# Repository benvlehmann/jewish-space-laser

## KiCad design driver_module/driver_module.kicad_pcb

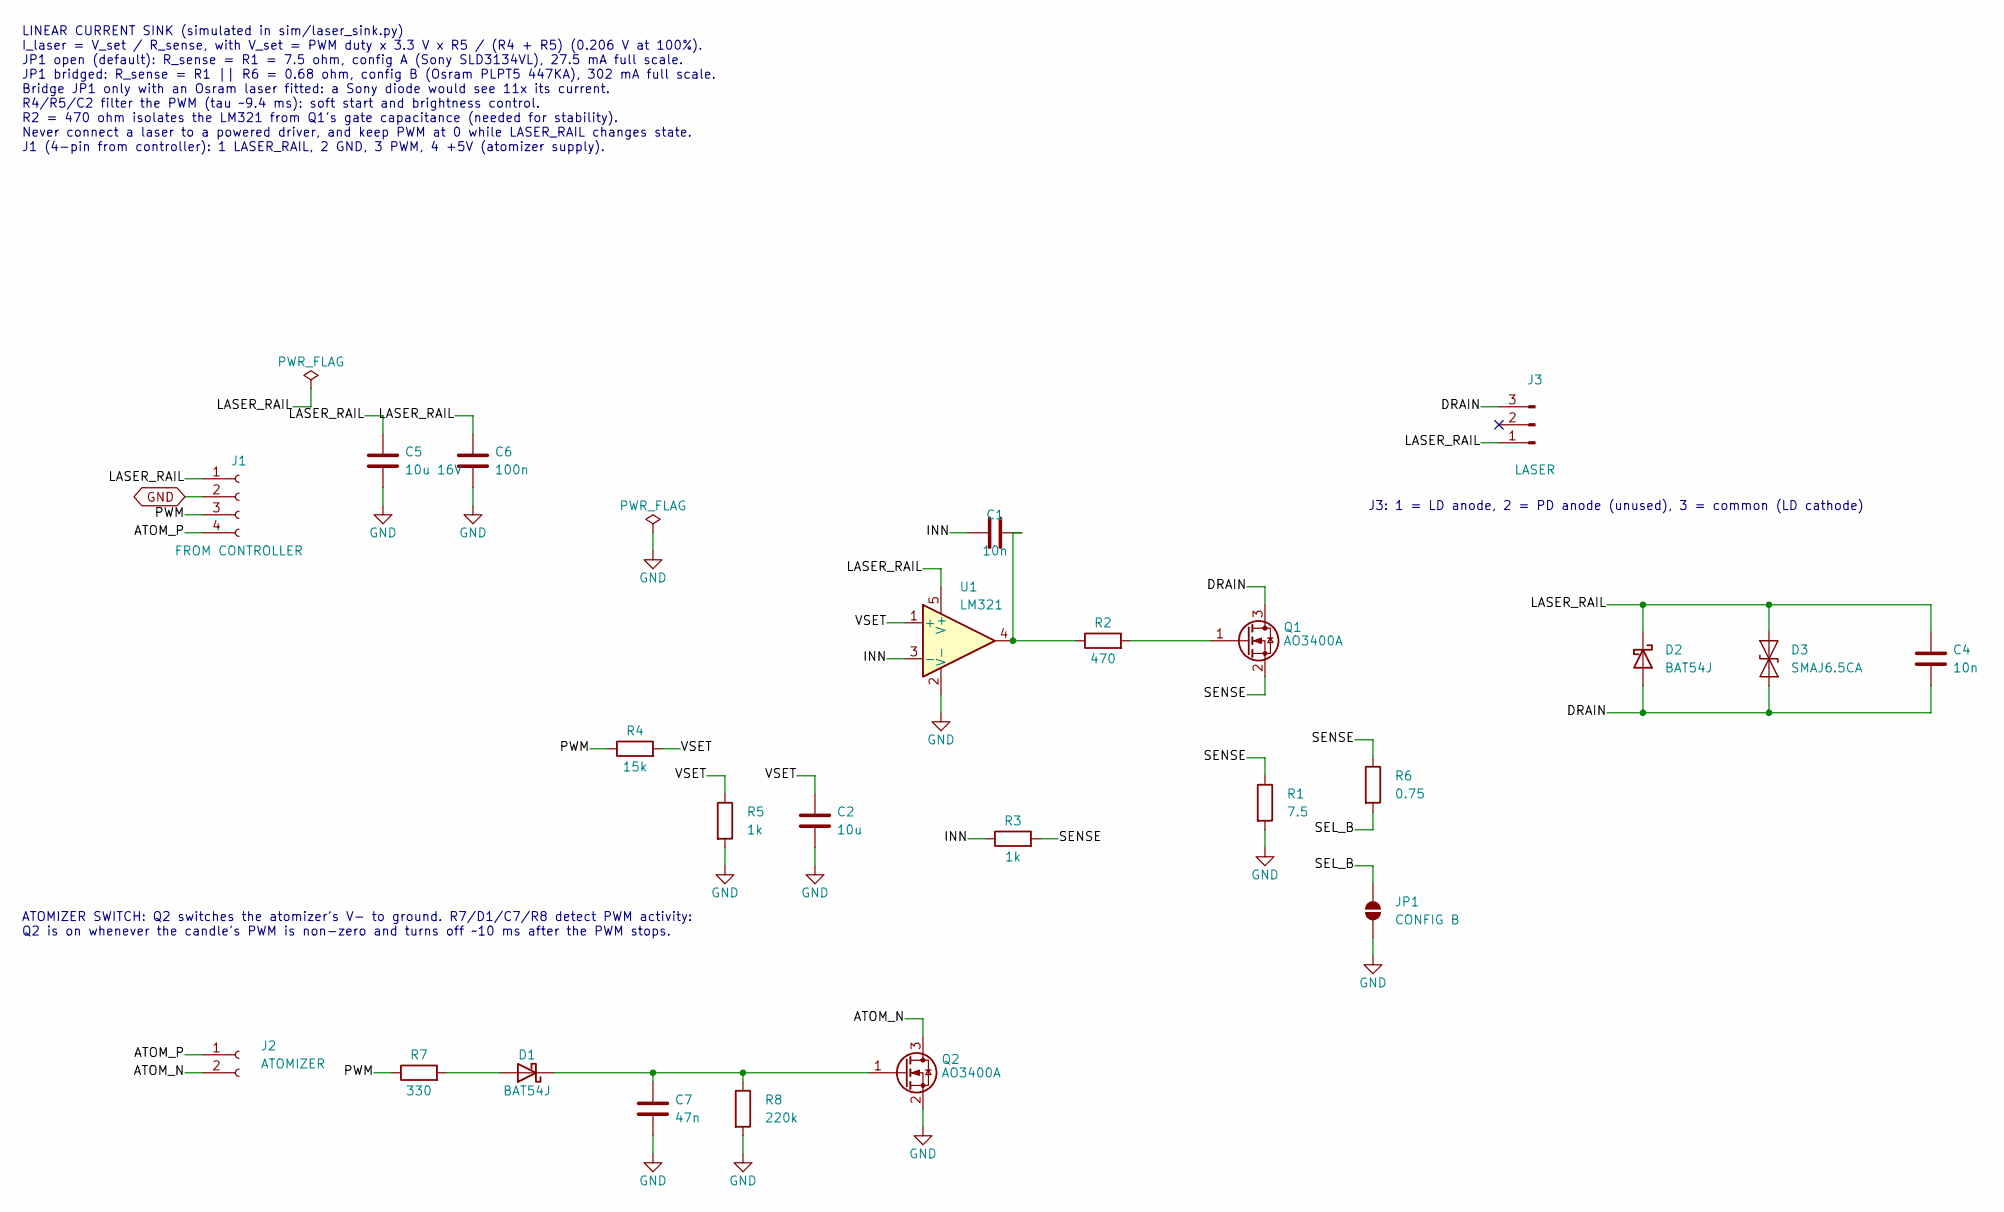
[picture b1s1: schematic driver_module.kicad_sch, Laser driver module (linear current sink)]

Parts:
C1, C4: 10n; C_0805_2012Metric_Pad1.18x1.45mm_HandSolder
C2: 10u; C_0805_2012Metric_Pad1.18x1.45mm_HandSolder
C5: 10u 16V; C_0805_2012Metric_Pad1.18x1.45mm_HandSolder
C6: 100n; C_0805_2012Metric_Pad1.18x1.45mm_HandSolder
C7: 47n; C_0805_2012Metric_Pad1.18x1.45mm_HandSolder
D1, D2: BAT54J; D_SOD-323F
D3: SMAJ6.5CA; D_SMA
J1: FROM CONTROLLER; JST_ZH_B4B-ZR_1x04_P1.50mm_Vertical
J2: ATOMIZER; JST_ZH_B2B-ZR_1x02_P1.50mm_Vertical
J3: LASER; JST_ZH_B3B-ZR_1x03_P1.50mm_Vertical
JP1: CONFIG B; SolderJumper-2_P1.3mm_Open_RoundedPad1.0x1.5mm
Q1, Q2: AO3400A; SOT-23
R1: 7.5; R_0805_2012Metric_Pad1.20x1.40mm_HandSolder
R2: 470; R_0805_2012Metric_Pad1.20x1.40mm_HandSolder
R3, R5: 1k; R_0805_2012Metric_Pad1.20x1.40mm_HandSolder
R4: 15k; R_0805_2012Metric_Pad1.20x1.40mm_HandSolder
R6: 0.75; R_0805_2012Metric_Pad1.20x1.40mm_HandSolder
R7: 330; R_0805_2012Metric_Pad1.20x1.40mm_HandSolder
R8: 220k; R_0805_2012Metric_Pad1.20x1.40mm_HandSolder
U1: LM321; SOT-23-5

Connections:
/ATOM_N: J2.2, Q2.3 (D)
/ATOM_P: J1.4, J2.1
/DRAIN: C4.2, D2.2 (A), D3.2 (A2), J3.3, Q1.3 (D)
/INN: C1.1, R3.1, U1.3 (-)
/LASER_RAIL: C4.1, C5.1, C6.1, D2.1 (K), D3.1 (A1), J1.1, J3.1, U1.5 (V+)
/PWM: J1.3, R4.1, R7.1
/SEL_B: JP1.1 (A), R6.2
/SENSE: Q1.2 (S), R1.1, R3.2, R6.1
/VSET: C2.1, R4.2, R5.1, U1.1 (+)
GND: C2.2, C5.2, C6.2, C7.2, J1.2, JP1.2 (B), Q2.2 (S), R1.2, R5.2, R8.2, U1.2 (V-)
unnamed: C1.2, R2.1, U1.4
unnamed: D1.2 (A), R7.2
unnamed: C7.1, D1.1 (K), Q2.1 (G), R8.1
unnamed: Q1.1 (G), R2.2

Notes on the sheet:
LINEAR CURRENT SINK (simulated in sim/laser_sink.py) I_laser = V_set / R_sense, with V_set = PWM duty x 3.3 V x R5 / (R4 + R5) (0.206 V at 100%). JP1 open (default): R_sense = R1 = 7.5 ohm, config A (Sony SLD3134VL), 27.5 mA full scale. JP1 bridged: R_sense = R1 || R6 = 0.68 ohm, config B (Osram PL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
J3: 1 = LD anode, 2 = PD anode (unused), 3 = common (LD cathode)
ATOMIZER SWITCH: Q2 switches the atomizer's V- to ground. R7/D1/C7/R8 detect PWM activity: Q2 is on whenever the candle's PWM is non-zero and turns off ~10 ms after the PWM stops.

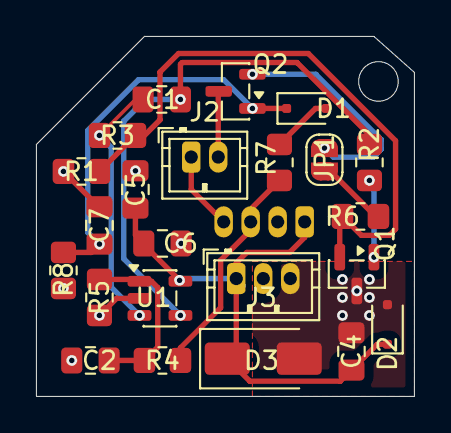
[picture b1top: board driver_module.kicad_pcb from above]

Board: 2 copper layers, 21.0 x 20.0 mm, 25 parts (1 on the bottom side), 14 nets.

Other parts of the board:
H1: MountingHole_2.2mm_M2

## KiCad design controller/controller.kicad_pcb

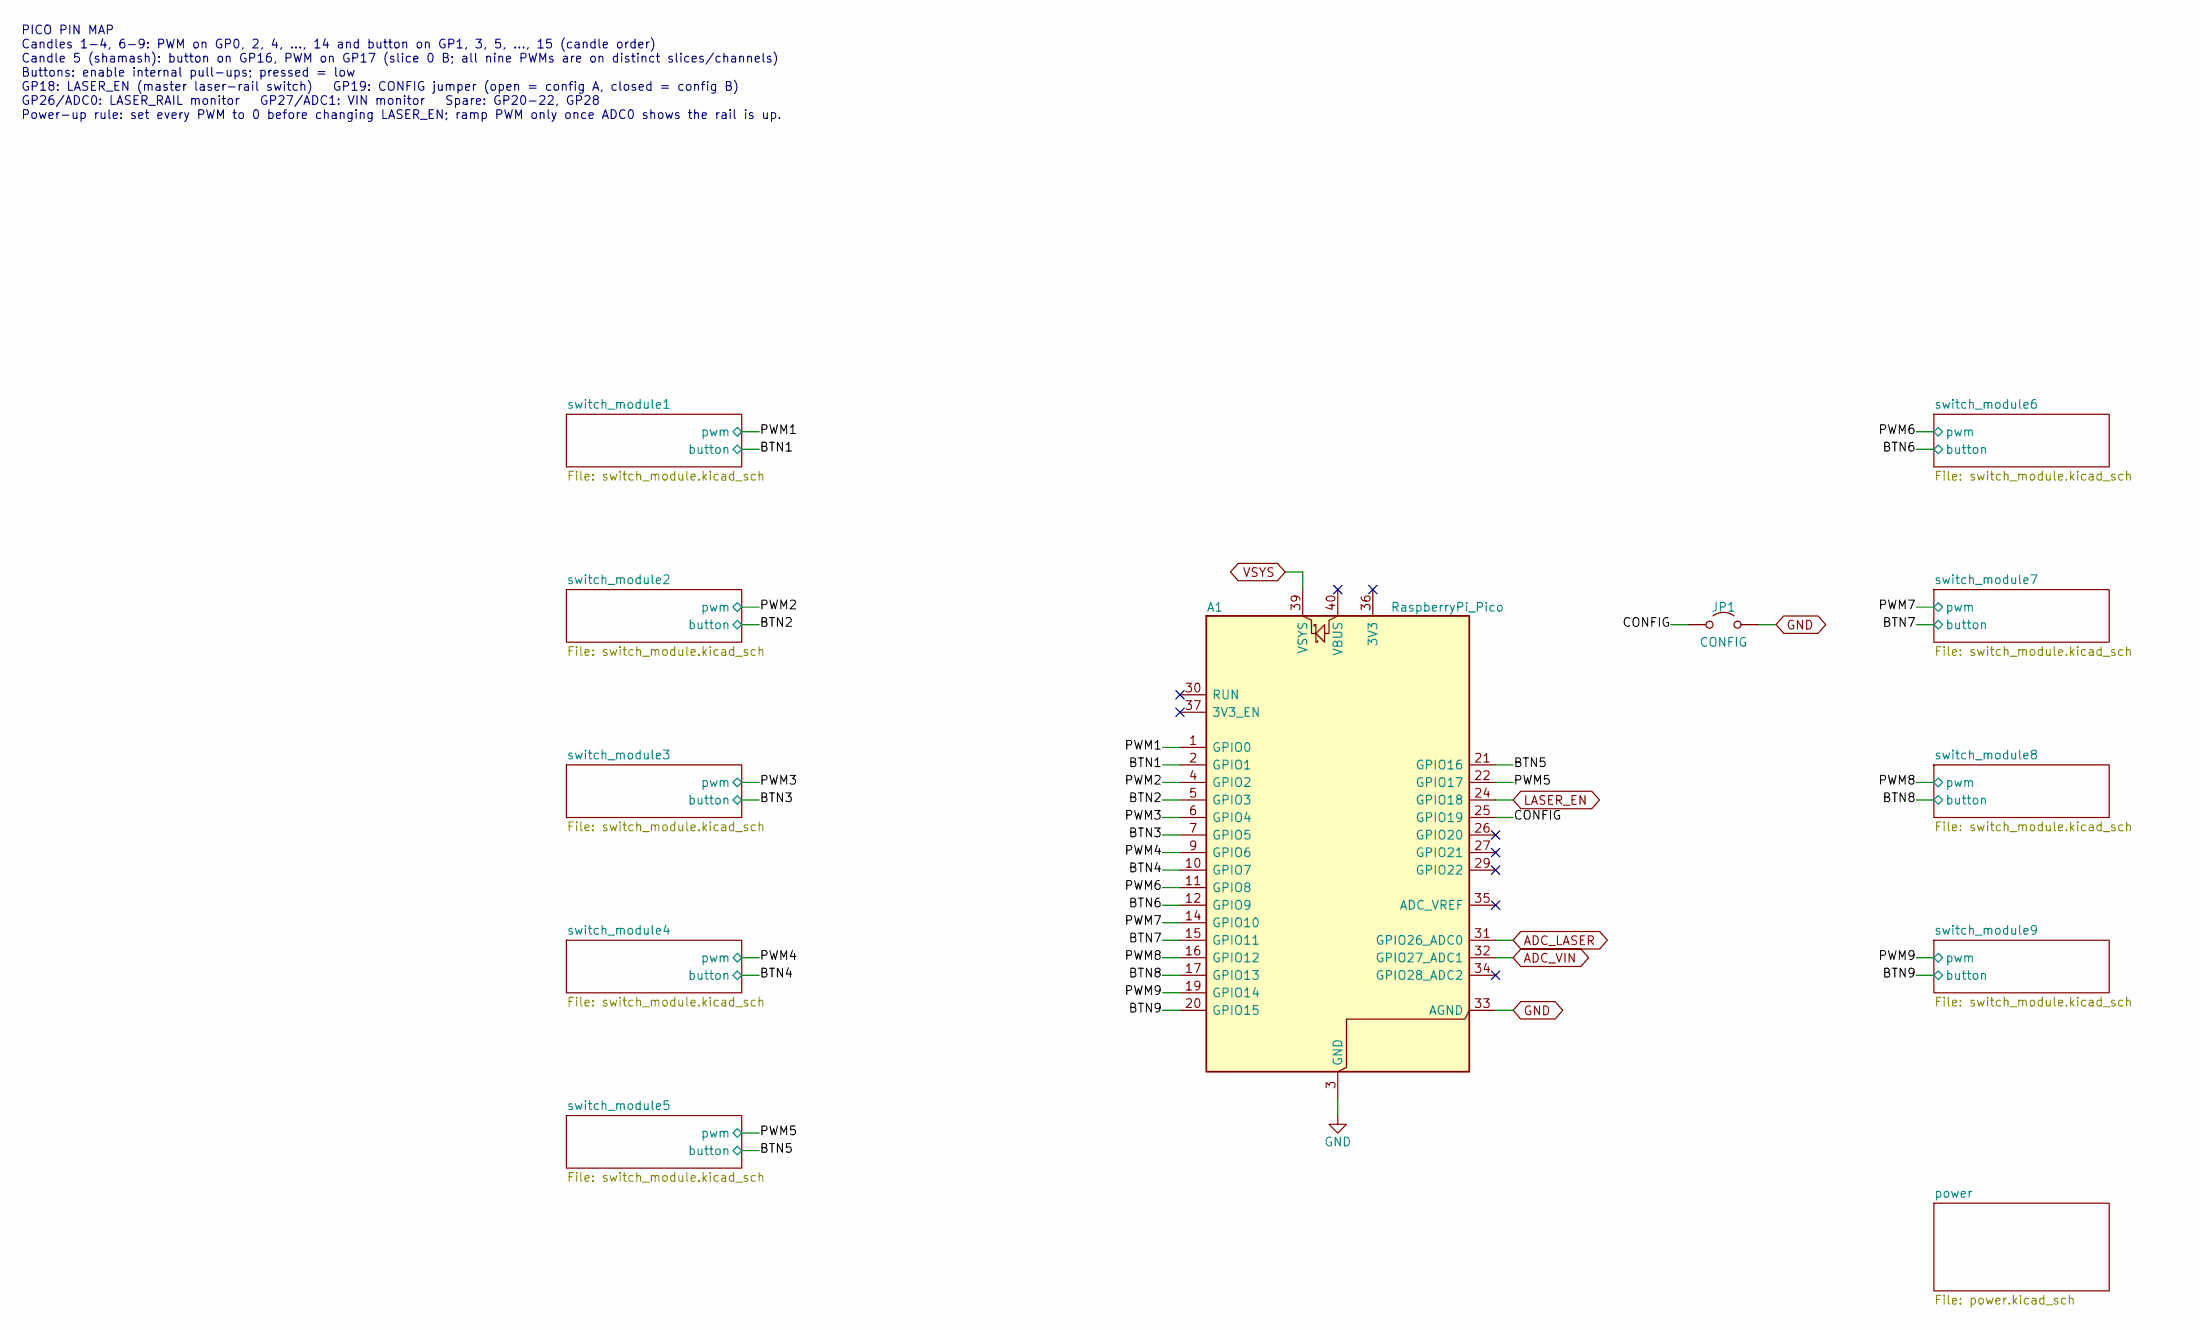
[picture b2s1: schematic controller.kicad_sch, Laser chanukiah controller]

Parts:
A1: RaspberryPi_Pico; RaspberryPi_Pico_Common_Unspecified
JP1: CONFIG; PinHeader_1x02_P2.54mm_Vertical

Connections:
/BTN1: A1.2 (GPIO1); also elsewhere on the board
/BTN2: A1.5 (GPIO3); also elsewhere on the board
/BTN3: A1.7 (GPIO5); also elsewhere on the board
/BTN4: A1.10 (GPIO7); also elsewhere on the board
/BTN5: A1.21 (GPIO16); also elsewhere on the board
/BTN6: A1.12 (GPIO9); also elsewhere on the board
/BTN7: A1.15 (GPIO11); also elsewhere on the board
/BTN8: A1.17 (GPIO13); also elsewhere on the board
/BTN9: A1.20 (GPIO15); also elsewhere on the board
/CONFIG: A1.25 (GPIO19), JP1.1 (A)
/PWM1: A1.1 (GPIO0); also elsewhere on the board
/PWM2: A1.4 (GPIO2); also elsewhere on the board
/PWM3: A1.6 (GPIO4); also elsewhere on the board
/PWM4: A1.9 (GPIO6); also elsewhere on the board
/PWM5: A1.22 (GPIO17); also elsewhere on the board
/PWM6: A1.11 (GPIO8); also elsewhere on the board
/PWM7: A1.14 (GPIO10); also elsewhere on the board
/PWM8: A1.16 (GPIO12); also elsewhere on the board
/PWM9: A1.19 (GPIO14); also elsewhere on the board
ADC_LASER: A1.31 (GPIO26_ADC0); also elsewhere on the board
ADC_VIN: A1.32 (GPIO27_ADC1); also elsewhere on the board
GND: A1.3 (GND), A1.8 (GND), A1.13 (GND), A1.18 (GND), A1.23 (GND), A1.28 (GND), A1.33 (AGND), A1.38 (GND), JP1.2 (B); also elsewhere on the board
LASER_EN: A1.24 (GPIO18); also elsewhere on the board
VSYS: A1.39 (VSYS); also elsewhere on the board

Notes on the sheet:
PICO PIN MAP Candles 1-4, 6-9: PWM on GP0, 2, 4, ..., 14 and button on GP1, 3, 5, ..., 15 (candle order) Candle 5 (shamash): button on GP16, PWM on GP17 (slice 0 B; all nine PWMs are on distinct slices/channels) Buttons: enable internal pull-ups; pressed = low GP18: LASER_EN (master laser-rail swit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

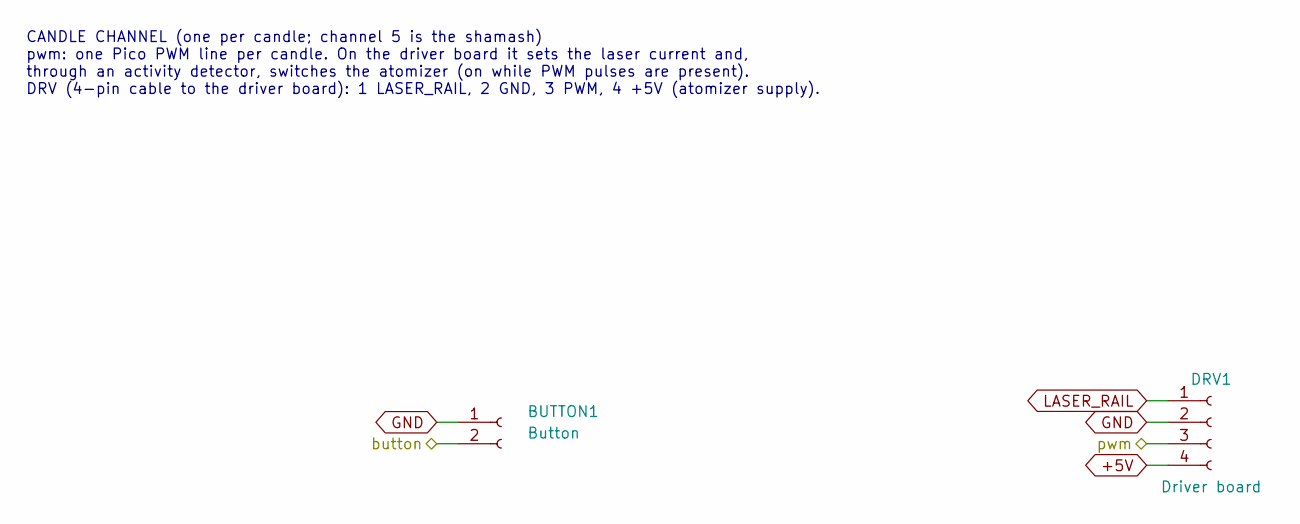
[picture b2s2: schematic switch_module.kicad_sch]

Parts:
BUTTON1: Button; JST_ZH_B2B-ZR_1x02_P1.50mm_Vertical
DRV1: Driver board; JST_ZH_B4B-ZR_1x04_P1.50mm_Vertical

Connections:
+5V: DRV1.4; also elsewhere on the board
/BTN1: BUTTON1.2; also elsewhere on the board
/PWM1: DRV1.3; also elsewhere on the board
GND: BUTTON1.1, DRV1.2; also elsewhere on the board
LASER_RAIL: DRV1.1; also elsewhere on the board

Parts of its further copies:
BUTTON2, BUTTON3, BUTTON4, BUTTON5, BUTTON6, BUTTON7, BUTTON8, BUTTON9: Button; JST_ZH_B2B-ZR_1x02_P1.50mm_Vertical
DRV2, DRV3, DRV4, DRV5, DRV6, DRV7, DRV8, DRV9: Driver board; JST_ZH_B4B-ZR_1x04_P1.50mm_Vertical

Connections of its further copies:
+5V: DRV2.4, DRV3.4, DRV4.4, DRV5.4, DRV6.4, DRV7.4, DRV8.4, DRV9.4; also elsewhere on the board
/BTN2: BUTTON2.2; also elsewhere on the board
/BTN3: BUTTON3.2; also elsewhere on the board
/BTN4: BUTTON4.2; also elsewhere on the board
/BTN5: BUTTON5.2; also elsewhere on the board
/BTN6: BUTTON6.2; also elsewhere on the board
/BTN7: BUTTON7.2; also elsewhere on the board
/BTN8: BUTTON8.2; also elsewhere on the board
/BTN9: BUTTON9.2; also elsewhere on the board
/PWM2: DRV2.3; also elsewhere on the board
/PWM3: DRV3.3; also elsewhere on the board
/PWM4: DRV4.3; also elsewhere on the board
/PWM5: DRV5.3; also elsewhere on the board
/PWM6: DRV6.3; also elsewhere on the board
/PWM7: DRV7.3; also elsewhere on the board
/PWM8: DRV8.3; also elsewhere on the board
/PWM9: DRV9.3; also elsewhere on the board
GND: BUTTON2.1, BUTTON3.1, BUTTON4.1, BUTTON5.1, BUTTON6.1, BUTTON7.1, BUTTON8.1, BUTTON9.1, DRV2.2, DRV3.2, DRV4.2, DRV5.2, DRV6.2, DRV7.2, DRV8.2, DRV9.2; also elsewhere on the board
LASER_RAIL: DRV2.1, DRV3.1, DRV4.1, DRV5.1, DRV6.1, DRV7.1, DRV8.1, DRV9.1; also elsewhere on the board

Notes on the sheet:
CANDLE CHANNEL (one per candle; channel 5 is the shamash) pwm: one Pico PWM line per candle. On the driver board it sets the laser current and, through an activity detector, switches the atomizer (on while PWM pulses are present). DRV (4-pin cable to the driver board): 1 LASER_RAIL, 2 GND, 3 PWM, 4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

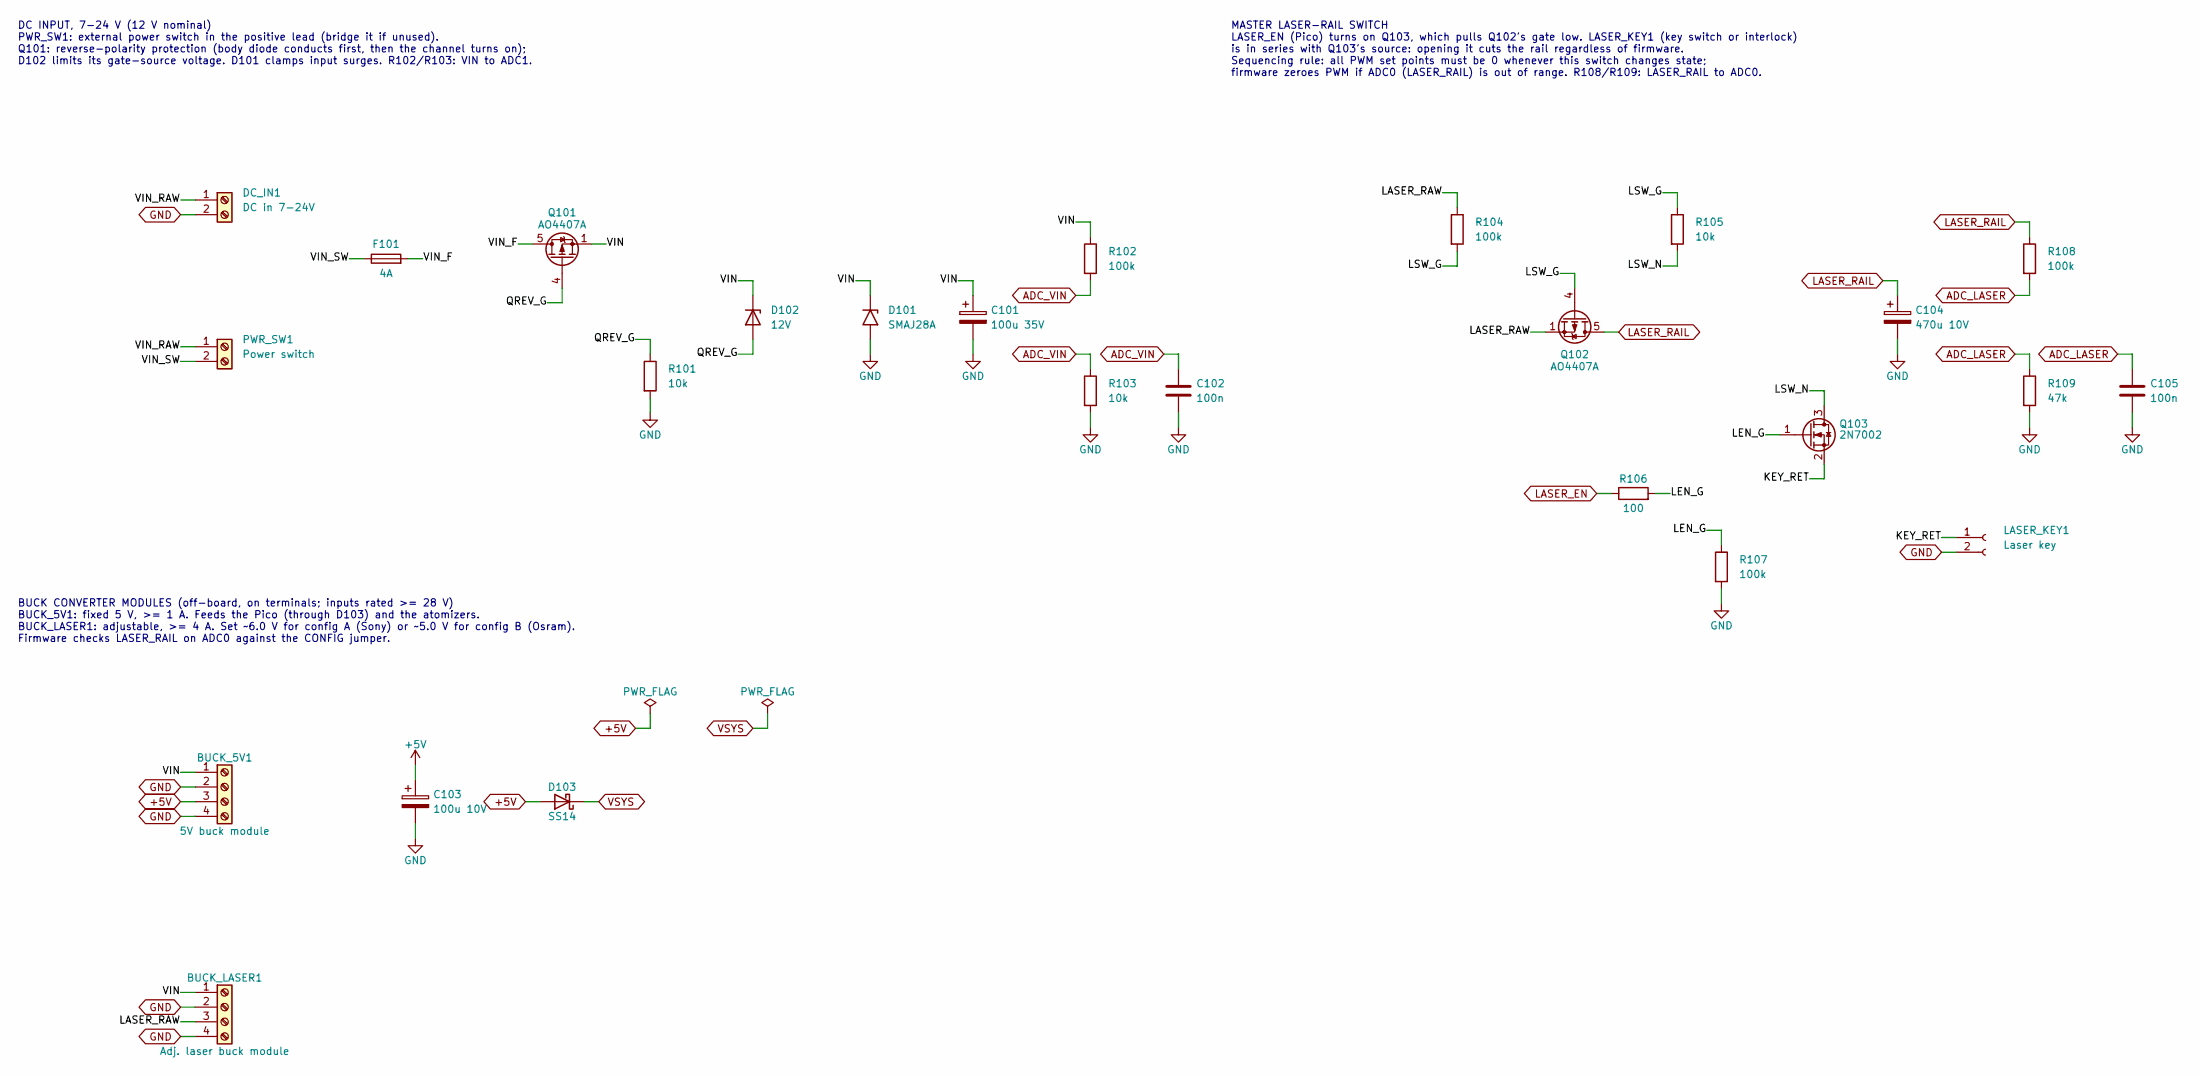
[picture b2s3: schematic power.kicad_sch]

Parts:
BUCK_5V1: 5V buck module; TerminalBlock_4Ucon_1x04_P3.50mm_Horizontal
BUCK_LASER1: Adj. laser buck module; TerminalBlock_4Ucon_1x04_P3.50mm_Horizontal
C101: 100u 35V; CP_Elec_8x10.5
C102, C105: 100n; C_0805_2012Metric_Pad1.18x1.45mm_HandSolder
C103: 100u 10V; CP_Elec_6.3x7.7
C104: 470u 10V; CP_Elec_8x10.5
D101: SMAJ28A; D_SMA
D102: 12V; D_SOD-123
D103: SS14; D_SMA
DC_IN1: DC in 7-24V; TerminalBlock_4Ucon_1x02_P3.50mm_Horizontal
F101: 4A; Fuse_1206_3216Metric_Pad1.42x1.75mm_HandSolder
LASER_KEY1: Laser key; JST_ZH_B2B-ZR_1x02_P1.50mm_Vertical
PWR_SW1: Power switch; TerminalBlock_4Ucon_1x02_P3.50mm_Horizontal
Q101, Q102: AO4407A; SOIC-8_3.9x4.9mm_P1.27mm
Q103: 2N7002; SOT-23
R101, R103, R105: 10k; R_0805_2012Metric_Pad1.20x1.40mm_HandSolder
R102, R104, R107, R108: 100k; R_0805_2012Metric_Pad1.20x1.40mm_HandSolder
R106: 100; R_0805_2012Metric_Pad1.20x1.40mm_HandSolder
R109: 47k; R_0805_2012Metric_Pad1.20x1.40mm_HandSolder

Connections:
+5V: BUCK_5V1.3, C103.1, D103.2 (A); also elsewhere on the board
/power/KEY_RET: LASER_KEY1.1, Q103.2 (S)
/power/LASER_RAW: BUCK_LASER1.3, Q102.1 (S), Q102.2 (S), Q102.3 (S), R104.1
/power/LEN_G: Q103.1 (G), R106.2, R107.1
/power/LSW_G: Q102.4 (G), R104.2, R105.1
/power/LSW_N: Q103.3 (D), R105.2
/power/QREV_G: D102.2 (A), Q101.4 (G), R101.1
/power/VIN: BUCK_5V1.1, BUCK_LASER1.1, C101.1, D101.1 (A1), D102.1 (K), Q101.1 (S), Q101.2 (S), Q101.3 (S), R102.1
/power/VIN_F: F101.2, Q101.5 (D), Q101.6 (D), Q101.7 (D), Q101.8 (D)
/power/VIN_RAW: DC_IN1.1, PWR_SW1.1
/power/VIN_SW: F101.1, PWR_SW1.2
ADC_LASER: C105.1, R108.2, R109.1; also elsewhere on the board
ADC_VIN: C102.1, R102.2, R103.1; also elsewhere on the board
GND: BUCK_5V1.2, BUCK_5V1.4, BUCK_LASER1.2, BUCK_LASER1.4, C101.2, C102.2, C103.2, C104.2, C105.2, D101.2 (A2), DC_IN1.2, LASER_KEY1.2, R101.2, R103.2, R107.2, R109.2; also elsewhere on the board
LASER_EN: R106.1; also elsewhere on the board
LASER_RAIL: C104.1, Q102.5 (D), Q102.6 (D), Q102.7 (D), Q102.8 (D), R108.1; also elsewhere on the board
VSYS: D103.1 (K); also elsewhere on the board

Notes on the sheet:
DC INPUT, 7-24 V (12 V nominal) PWR_SW1: external power switch in the positive lead (bridge it if unused). Q101: reverse-polarity protection (body diode conducts first, then the channel turns on); D102 limits its gate-source voltage. D101 clamps input surges. R102/R103: VIN to ADC1.
BUCK CONVERTER MODULES (off-board, on terminals; inputs rated >= 28 V) BUCK_5V1: fixed 5 V, >= 1 A. Feeds the Pico (through D103) and the atomizers. BUCK_LASER1: adjustable, >= 4 A. Set ~6.0 V for config A (Sony) or ~5.0 V for config B (Osram). Firmware checks LASER_RAIL on ADC0 against the CONFIG 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
MASTER LASER-RAIL SWITCH LASER_EN (Pico) turns on Q103, which pulls Q102's gate low. LASER_KEY1 (key switch or interlock) is in series with Q103's source: opening it cuts the rail regardless of firmware. Sequencing rule: all PWM set points must be 0 whenever this switch changes state; firmware zero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

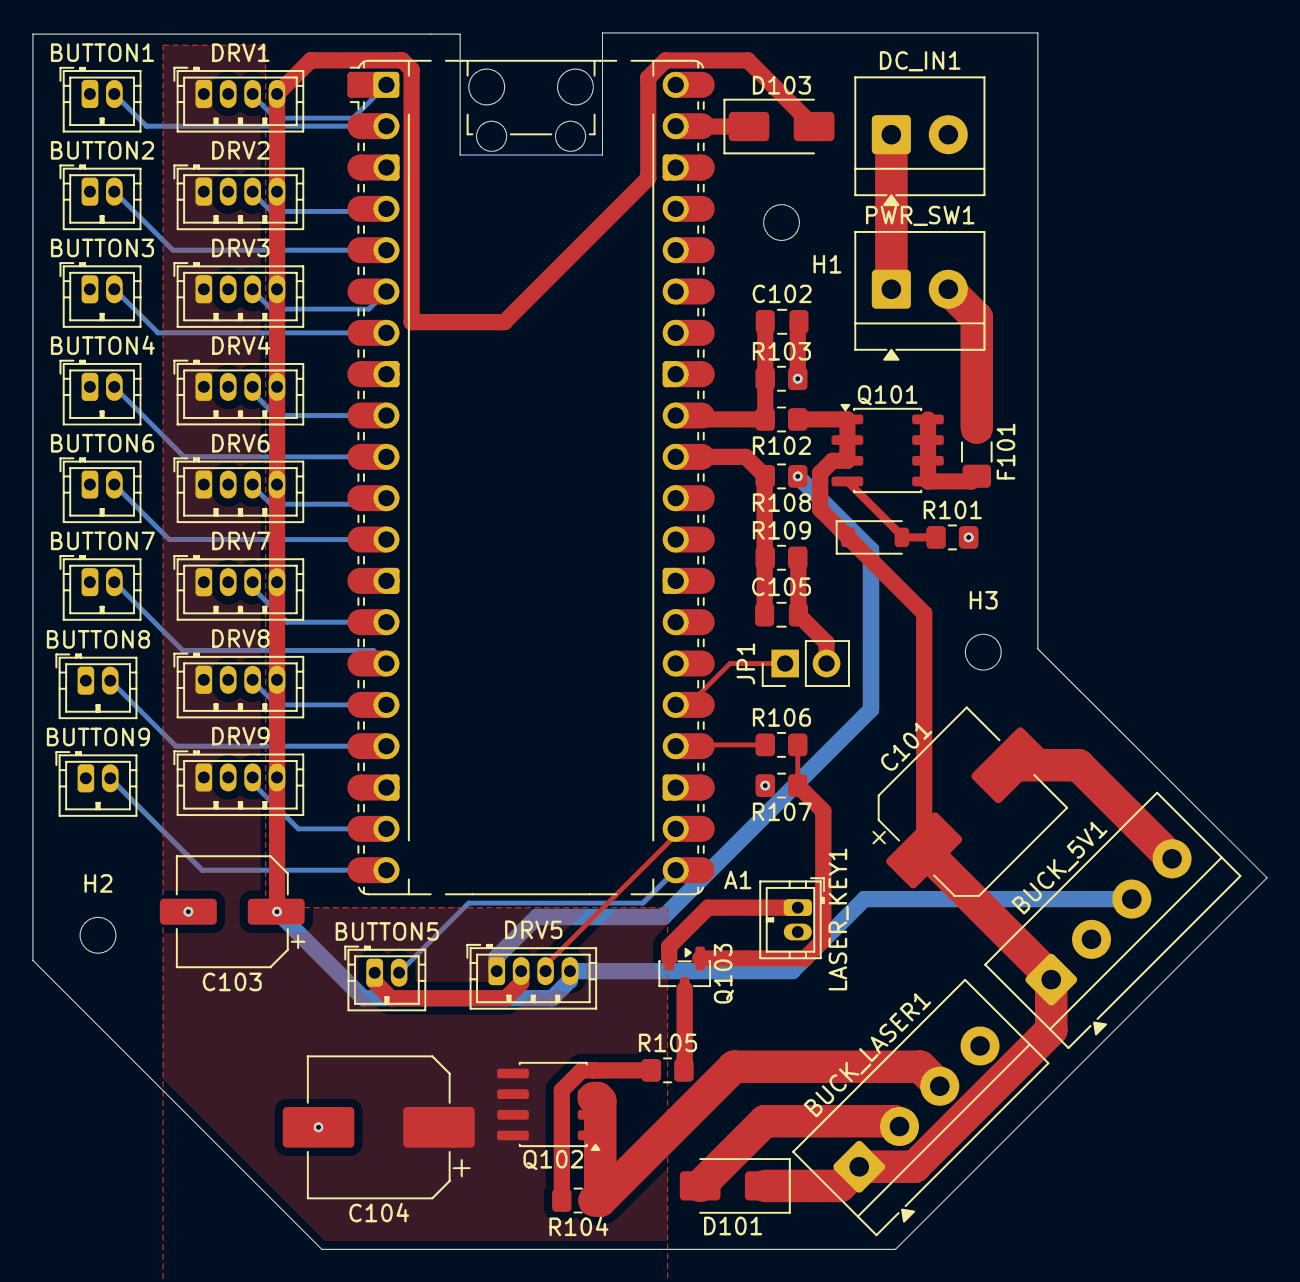
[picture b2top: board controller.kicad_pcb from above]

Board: 2 copper layers, 75.8 x 74.8 mm, 49 parts (0 on the bottom side), 36 nets.

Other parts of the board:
H1, H2, H3: MountingHole_2.2mm_M2
